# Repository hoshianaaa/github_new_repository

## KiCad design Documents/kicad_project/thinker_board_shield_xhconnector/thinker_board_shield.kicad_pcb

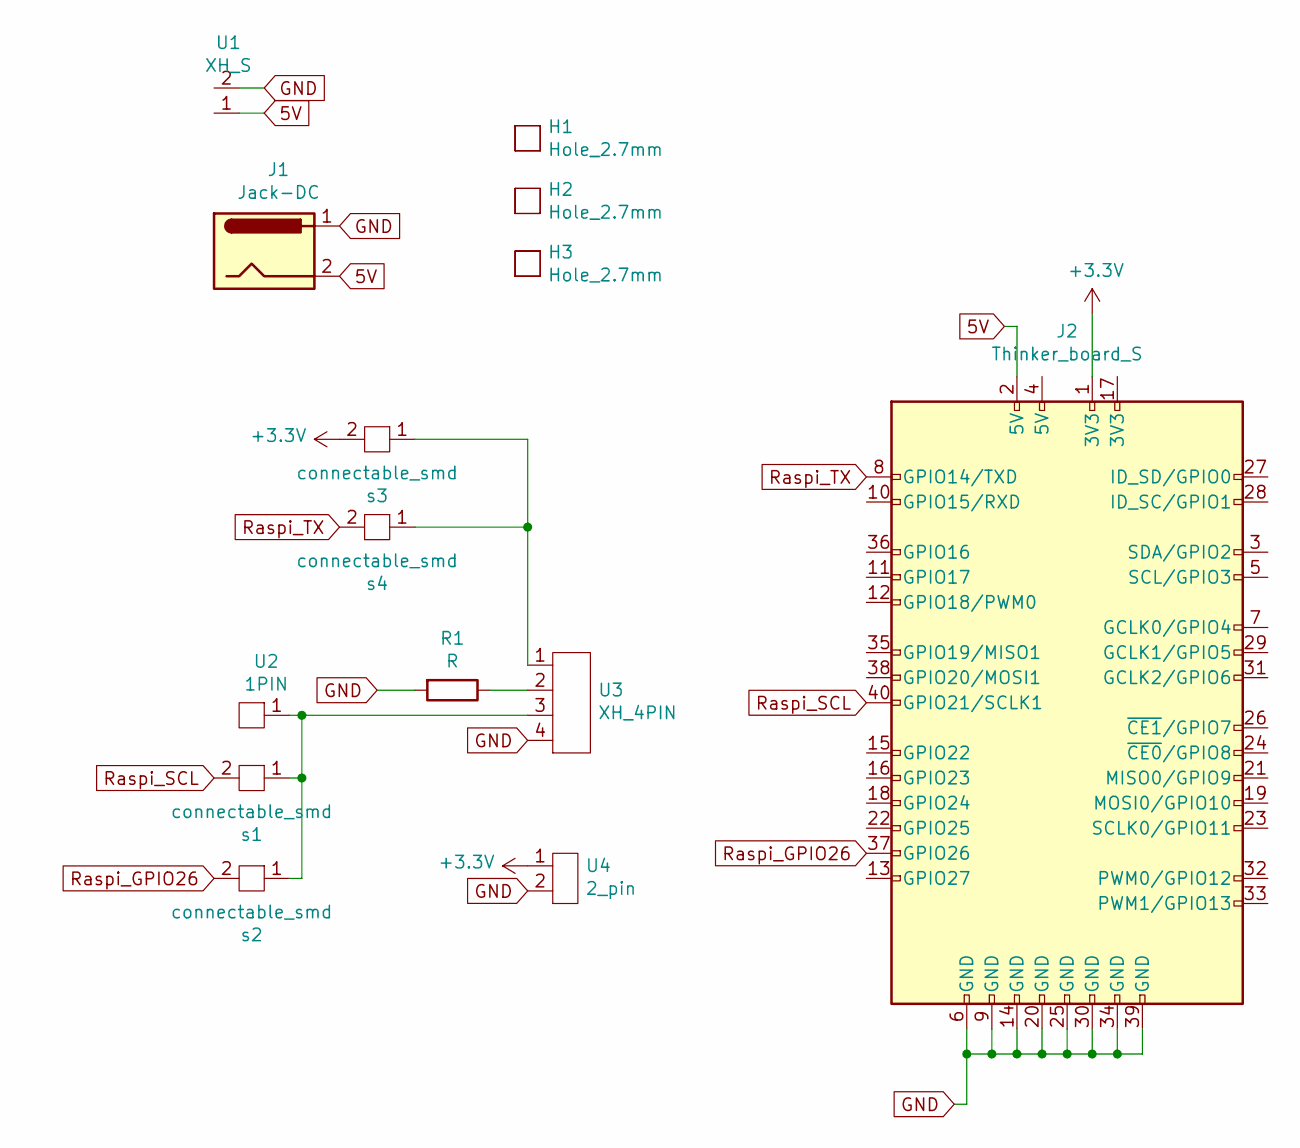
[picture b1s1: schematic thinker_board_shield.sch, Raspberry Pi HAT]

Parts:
H1, H2, H3: Hole_2.7mm
J1: Jack-DC; DCJ
J2: Thinker_board_S; Thinker_board_pin
R1: R; register_0603
U1: XH_S; S2B-XH-A
U2: 1PIN
U3: XH_4PIN; XH4PIN_S
U4: 2_pin
s1, s2, s3, s4: connectable_smd

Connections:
5V: J1.2, J2.2 (5V), U1.1
+3V3: J2.1 (3V3), U4.1, s3.2
GND: J1.1, J2.6 (GND), J2.9 (GND), J2.14 (GND), J2.20 (GND), J2.25 (GND), J2.30 (GND), J2.34 (GND), J2.39 (GND), R1.2, U1.2, U3.4, U4.2
unnamed: R1.1, U3.2
unnamed: U2.1, U3.3, s1.1, s2.1
unnamed: U3.1, s3.1, s4.1
Raspi_GPIO26: J2.37 (GPIO26), s2.2
Raspi_SCL: J2.40 (GPIO21/SCLK1), s1.2
Raspi_TX: J2.8 (GPIO14/TXD), s4.2

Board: 4 copper layers, 14 parts (5 on the bottom side), 9 nets, no tracks yet.

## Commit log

2019-09-06 kansei
2019-09-11 add big wire /before auto-router
2019-09-11 add parts and set position
2019-09-11 make big wire /before auto-wire
2019-09-13 change to raspi
2019-10-04 remove all file
2019-10-04 make new file
2019-10-04 add new file
